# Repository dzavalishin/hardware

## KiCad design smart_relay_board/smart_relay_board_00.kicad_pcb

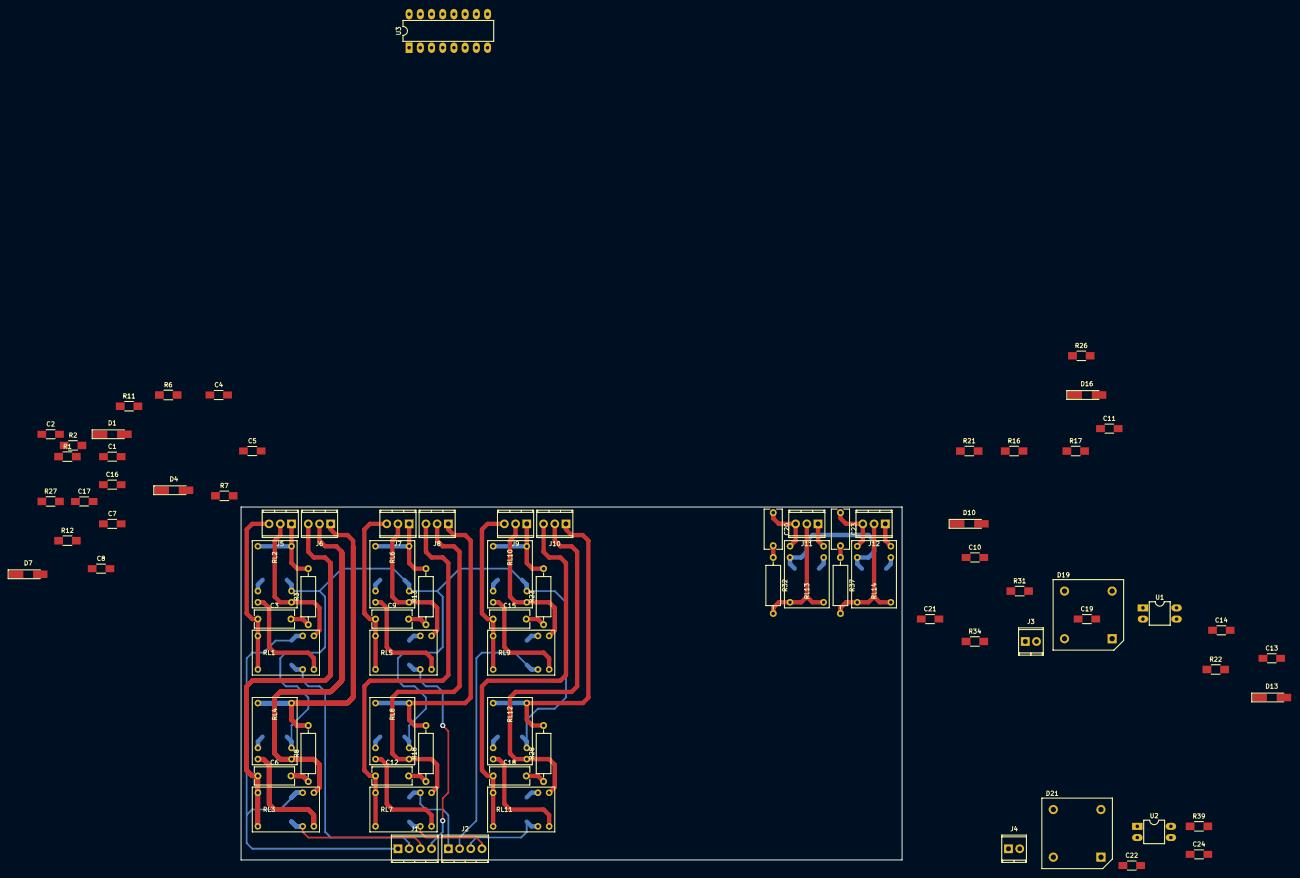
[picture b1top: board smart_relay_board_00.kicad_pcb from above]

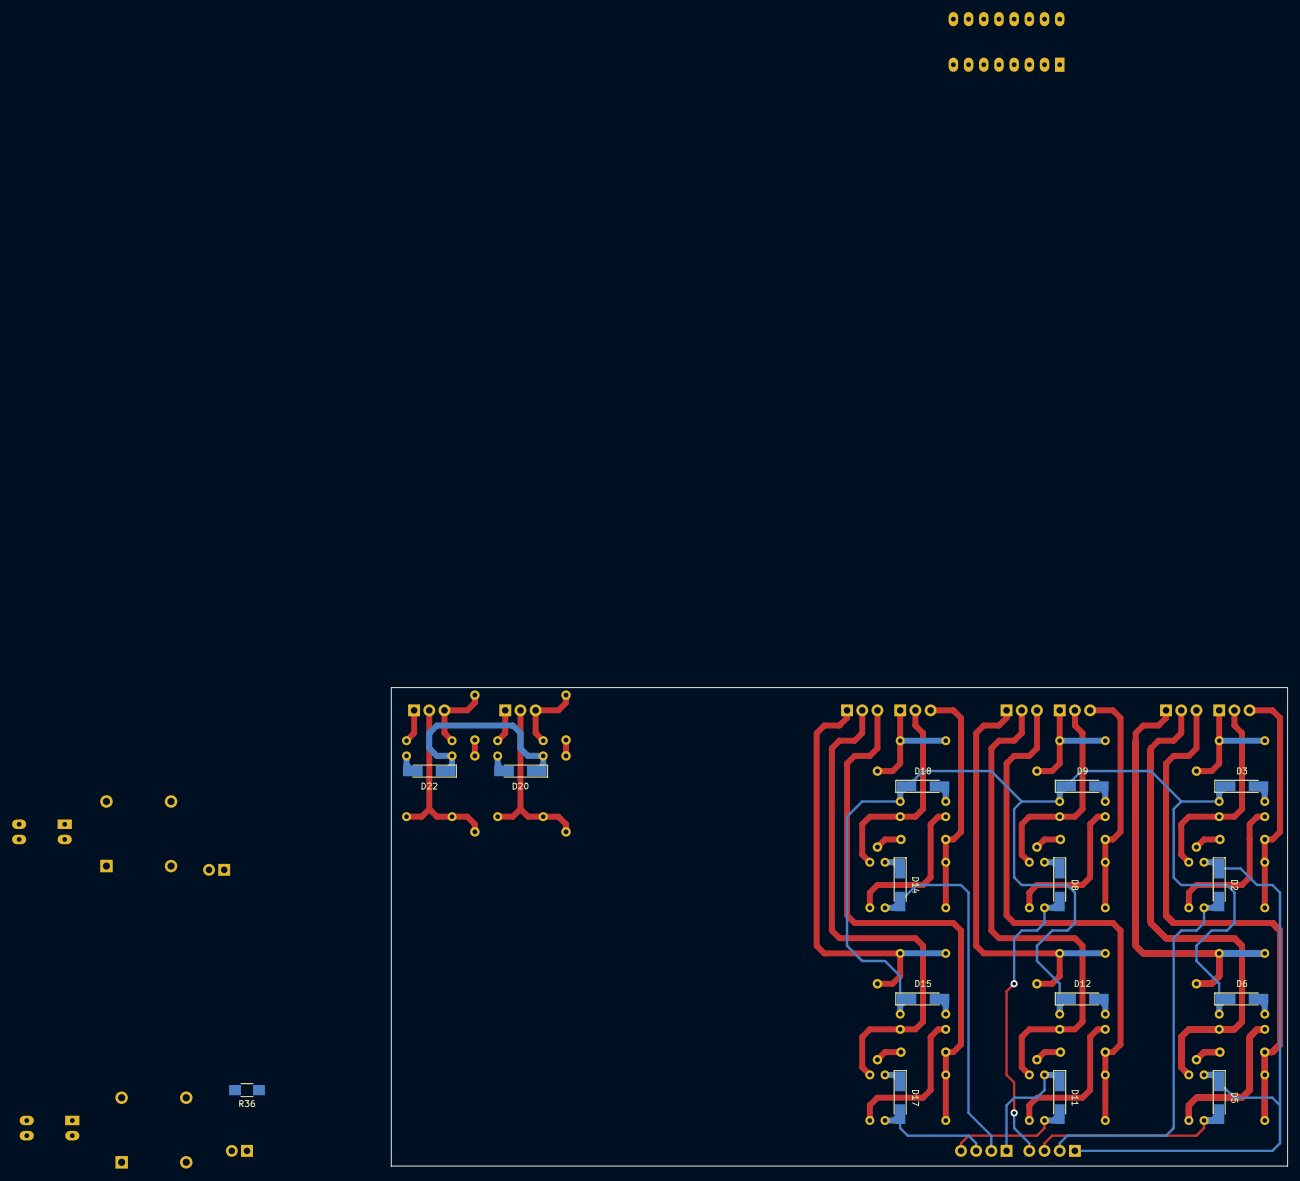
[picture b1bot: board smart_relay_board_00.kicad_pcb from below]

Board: 2 copper layers, 149.9 x 80.0 mm, 99 parts (15 on the bottom side), 81 nets.

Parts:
C1, C2, C4, C5, C7, C8, C10, C11, C13, C14, C16, C17, C19, C21, C22, C24: 0,1; C_1206_HandSoldering
C3, C6, C9, C12, C15, C18, C20, C23: 0,022 x 400v; C_Rect_L9.0mm_W4.0mm_P7.50mm_MKT
D1, D4, D7, D10, D13, D16: 4v7; D_MiniMELF_Handsoldering
D2, D3, D5, D6, D8, D9, D11, D12, D14, D15, D17, D18: 1n4148; D_MiniMELF_Handsoldering
D19, D21: D_Bridge_-A+A; Diode_Bridge_15.7x15.7
D20, D22: 1N4148; D_MiniMELF_Handsoldering
J1: Di0-2; TerminalBlock_Pheonix_MPT-2.54mm_4pol
J2: Di3-5; TerminalBlock_Pheonix_MPT-2.54mm_4pol
J3: Di_6; TerminalBlock_Pheonix_MPT-2.54mm_2pol
J4: Di_7; TerminalBlock_Pheonix_MPT-2.54mm_2pol
J5, J6, J7, J8, J9, J10: Do_Adv; TerminalBlock_Pheonix_MPT-2.54mm_3pol
J11, J12: Do; TerminalBlock_Pheonix_MPT-2.54mm_3pol
R1, R6, R11, R16, R21, R26, R31, R36: 22k; R_1206_HandSoldering
R2, R7, R12, R17, R22, R27, R34, R39: 1k; R_1206_HandSoldering
R3, R8, R13, R18, R23, R28, R32, R37: 100 1w; R_Axial_DIN0309_L9.0mm_D3.2mm_P12.70mm_Horizontal
RL1, RL2, RL3, RL4, RL5, RL6, RL7, RL8, RL9, RL10, RL11, RL12, RL13, RL14: HK4100F; Relay_SPDT_HK4100F
U1, U2: LTV-817; DIP-4_W7.62mm_LongPads
U3: 74HC595; DIP-16_W7.62mm_LongPads

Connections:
+5V: D3.1, D6.1, D9.1, D12.1, D15.1, D18.1, D20.1, D22.1, RL2.5, RL4.5, RL6.5, RL8.5, RL10.5, RL12.5, RL13.5, RL14.5
/Sheet_relay_pair_0/Relay_In_Minus: D2.2, J1.2, R1.1, RL1.2
/Sheet_relay_pair_0/Relay_In_Plus: D2.1, D5.1, D8.1, J1.1, RL1.5, RL3.5, RL5.5
/Sheet_relay_pair_1/Relay_In_Minus: D5.2, J1.3, R6.1, RL3.2
/Sheet_relay_pair_2/Relay_In_Minus: D8.2, J1.4, R11.1, RL5.2
/Sheet_relay_pair_3/Relay_In_Minus: D14.2, J2.2, R21.1, RL9.2
/Sheet_relay_pair_3/Relay_In_Plus: D11.1, D14.1, D17.1, J2.1, RL7.5, RL9.5, RL11.5
/Sheet_relay_pair_4/Relay_In_Minus: D17.2, J2.3, R26.1, RL11.2
/Sheet_relay_pair_5/Relay_In_Minus: D11.2, J2.4, R16.1, RL7.2
/Simple_Di_Do_6/DI_B: D19.2, J3.2
/Simple_Di_Do_6/Di_A: J3.1, R31.2
/Simple_Di_Do_7/DI_B: D21.2, J4.2
/Simple_Di_Do_7/Di_A: J4.1, R36.2
CPU_Di0: C2.1, R2.2
CPU_Di1: C5.1, R7.2
CPU_Di2: C8.1, R12.2
CPU_Di3: C14.1, R22.2
CPU_Di4: C17.1, R27.2
CPU_Di5: C11.1, R17.2
CPU_Di6: C21.1, R34.2
CPU_Di7: C24.1, R39.2
CPU_Do0: D3.2, RL2.2, U3.15
CPU_Do1: D6.2, RL4.2, U3.1
CPU_Do2: D9.2, RL6.2, U3.2
CPU_Do3: D15.2, D18.2, RL10.2, RL12.2, U3.3, U3.4
CPU_Do5: D12.2, RL8.2, U3.5
CPU_Do6: D20.2, RL13.2, U3.6
CPU_Do7: D22.2, RL14.2, U3.7
GND: C1.2, C2.2, C4.2, C5.2, C7.2, C8.2, C10.2, C11.2, C13.2, C14.2, C16.2, C17.2, C21.2, C24.2, D1.2, D4.2, D7.2, D10.2, D13.2, D16.2, U1.3, U2.3, U3.8
unnamed: C1.1, D1.1, R1.2, R2.1
unnamed: C3.1, J5.3, RL1.1, RL1.6
unnamed: C3.2, R3.1
unnamed: C4.1, D4.1, R6.2, R7.1
unnamed: C6.1, J6.3, RL3.1, RL3.6
unnamed: C6.2, R8.1
unnamed: C7.1, D7.1, R11.2, R12.1
unnamed: C9.1, J7.3, RL5.1, RL5.6
unnamed: C9.2, R13.1
unnamed: C10.1, D10.1, R16.2, R17.1
unnamed: C12.1, J8.3, RL7.1, RL7.6
unnamed: C12.2, R18.1
unnamed: C13.1, D13.1, R21.2, R22.1
unnamed: C15.1, J9.3, RL9.1, RL9.6
unnamed: C15.2, R23.1
unnamed: C16.1, D16.1, R26.2, R27.1
unnamed: C18.1, J10.3, RL11.1, RL11.6
unnamed: C18.2, R28.1
unnamed: C19.1, D19.3, U1.1
unnamed: C19.2, D19.1, U1.2
unnamed: C20.1, J11.3, RL13.4
unnamed: C20.2, R32.1
unnamed: C22.1, D21.3, U2.1
unnamed: C22.2, D21.1, U2.2
unnamed: C23.1, J12.3, RL14.4
unnamed: C23.2, R37.1
unnamed: D19.4, R31.1
unnamed: D21.4, R36.1
unnamed: J5.1, R3.2, RL2.1, RL2.6
unnamed: J5.2, RL1.4, RL2.4
unnamed: J6.1, R8.2, RL4.1, RL4.6
unnamed: J6.2, RL3.4, RL4.4
unnamed: J7.1, R13.2, RL6.1, RL6.6
unnamed: J7.2, RL5.4, RL6.4
unnamed: J8.1, R18.2, RL8.1, RL8.6
unnamed: J8.2, RL7.4, RL8.4
unnamed: J9.1, R23.2, RL10.1, RL10.6
unnamed: J9.2, RL9.4, RL10.4
unnamed: J10.1, R28.2, RL12.1, RL12.6
unnamed: J10.2, RL11.4, RL12.4
unnamed: J11.1, RL13.3
unnamed: J11.2, R32.2, RL13.1, RL13.6
unnamed: J12.1, RL14.3
unnamed: J12.2, R37.2, RL14.1, RL14.6
unnamed: R34.1, U1.4
unnamed: R39.1, U2.4
unnamed: RL1.3, RL2.3
unnamed: RL3.3, RL4.3
unnamed: RL5.3, RL6.3
unnamed: RL7.3, RL8.3
unnamed: RL9.3, RL10.3
unnamed: RL11.3, RL12.3

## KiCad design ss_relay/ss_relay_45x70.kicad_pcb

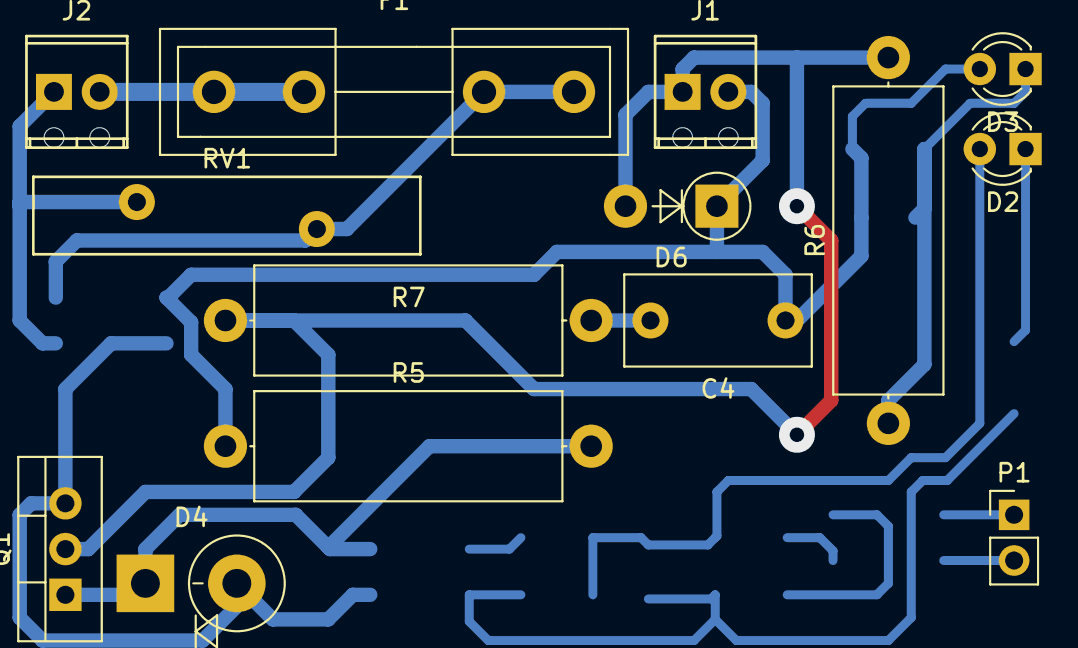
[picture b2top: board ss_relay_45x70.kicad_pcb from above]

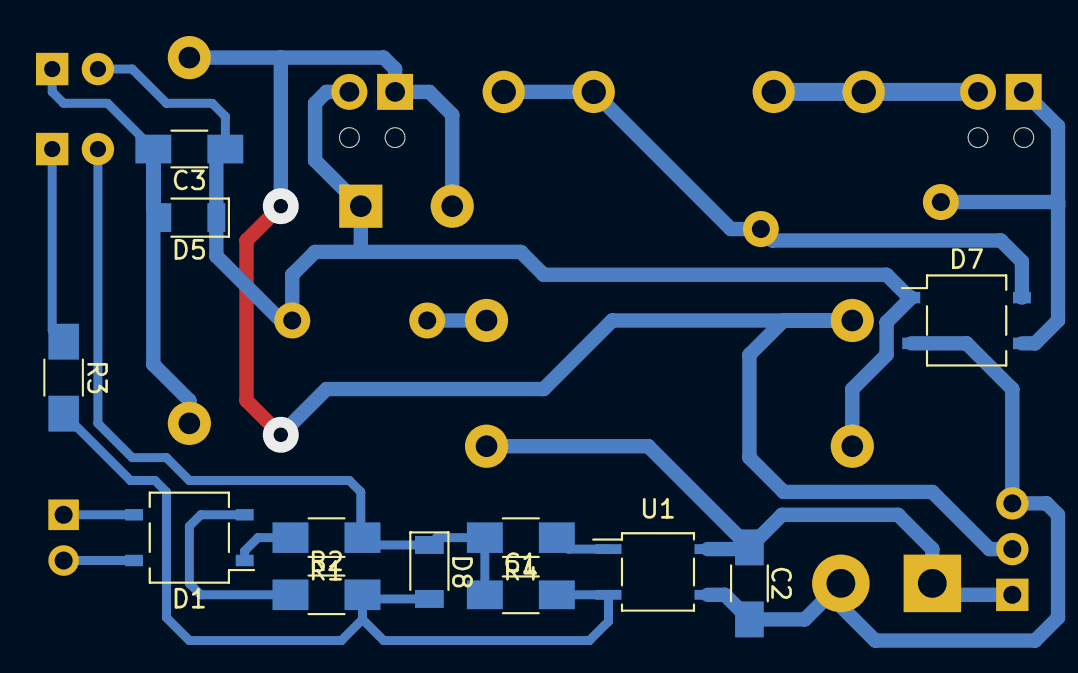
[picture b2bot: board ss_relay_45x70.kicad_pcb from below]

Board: 2 copper layers, 26 parts (12 on the bottom side), 17 nets.

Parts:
C1, C2, C3: 0,1; C_1206_HandSoldering
C4: 0,1 400v; C_Rect_L10.3mm_W5.0mm_P7.50mm_MKS4
D1, D7: MB6S; Diode_Bridge_TO-269AA
D2, D3: LED; LED_D3.0mm
D4: 7,5v 1500a; D_DO-201AD_P5.08mm_Vertical_KathodeUp
D5, D8: 5v6; D_1206
D6: RL206; D_DO-15_P5.08mm_Vertical_AnodeUp
F1: 0,5A; Fuseholder5x20_horiz_open_inline_Type-I
J1: DC Load; TerminalBlock_Pheonix_MPT-2.54mm_2pol
J2: AC220; TerminalBlock_Pheonix_MPT-2.54mm_2pol
P1: CONN_01X02; Pin_Header_Straight_1x02_Pitch2.54mm
Q1: IRF730; TO-220-3_Vertical
R1, R2: 560; R_1206_HandSoldering
R3, R4: 1k; R_1206_HandSoldering
R5, R6: 470k 1W; R_Axial_DIN0617_L17.0mm_D6.0mm_P20.32mm_Horizontal
R7: 56; R_Axial_DIN0617_L17.0mm_D6.0mm_P20.32mm_Horizontal
RV1: 14K391; RV_Disc_D21.5_W4.3_P10
U1: PC817; SOP-4_3.8x4.1mm_Pitch2.54mm

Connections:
unnamed: C1.1, D2.2, D8.1, R1.1, R4.2
unnamed: C1.2, D8.2, R2.2, R3.2, U1.2
unnamed: C2.1, D4.1, Q1.1, R5.2, U1.4
unnamed: C2.2, D4.2, D7.2, Q1.3, U1.3
unnamed: C3.1, C4.1, D3.2, D5.1, D6.1, D7.1, J1.2, R5.1
unnamed: C3.2, D3.1, D5.2, R6.1
unnamed: C4.2, R7.1
unnamed: D1.1, R1.2
unnamed: D1.2, R2.1
unnamed: D1.3, P1.1
unnamed: D1.4, P1.2
unnamed: D2.1, R3.1
unnamed: D6.2, J1.1, Q1.2, R6.2, R7.2
unnamed: D7.3, J2.1, RV1.2
unnamed: D7.4, F1.2, RV1.1
unnamed: F1.1, J2.2
unnamed: R4.1, U1.1

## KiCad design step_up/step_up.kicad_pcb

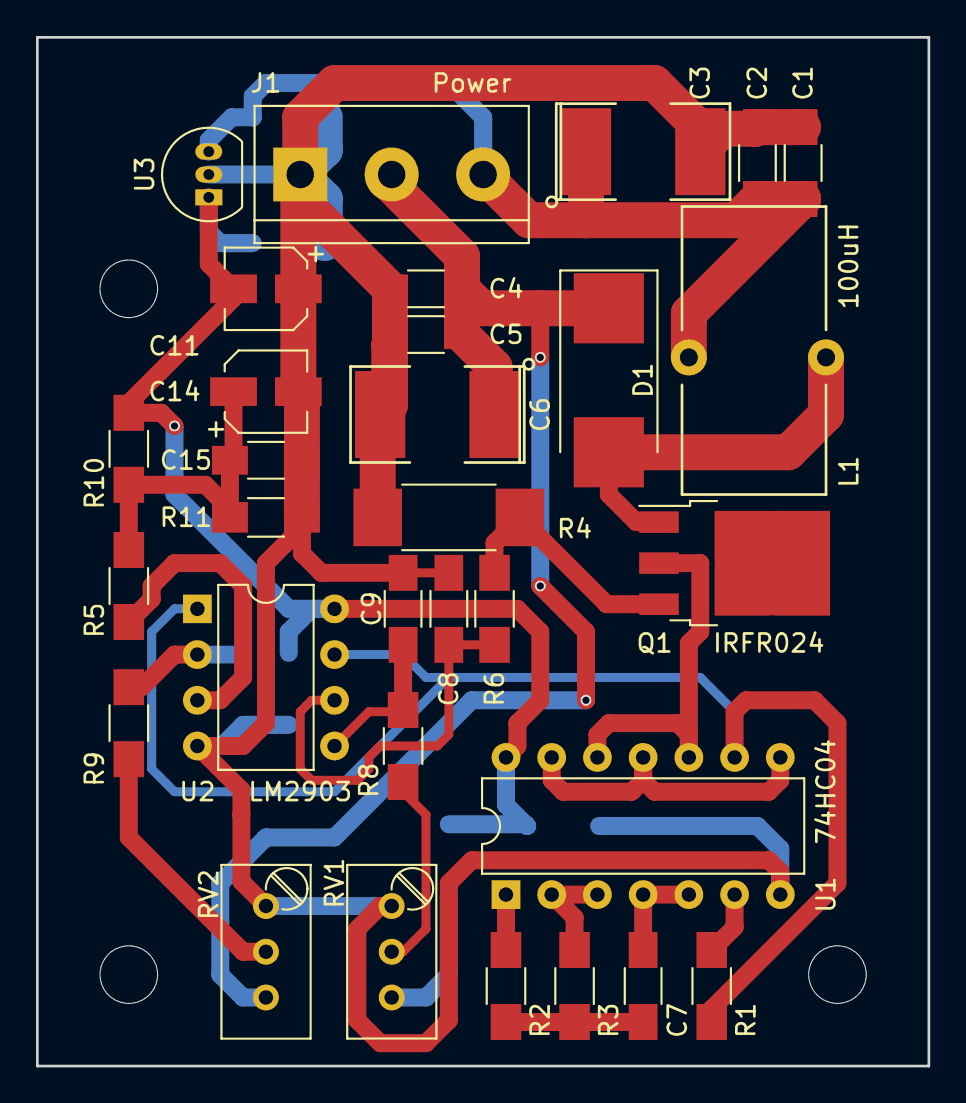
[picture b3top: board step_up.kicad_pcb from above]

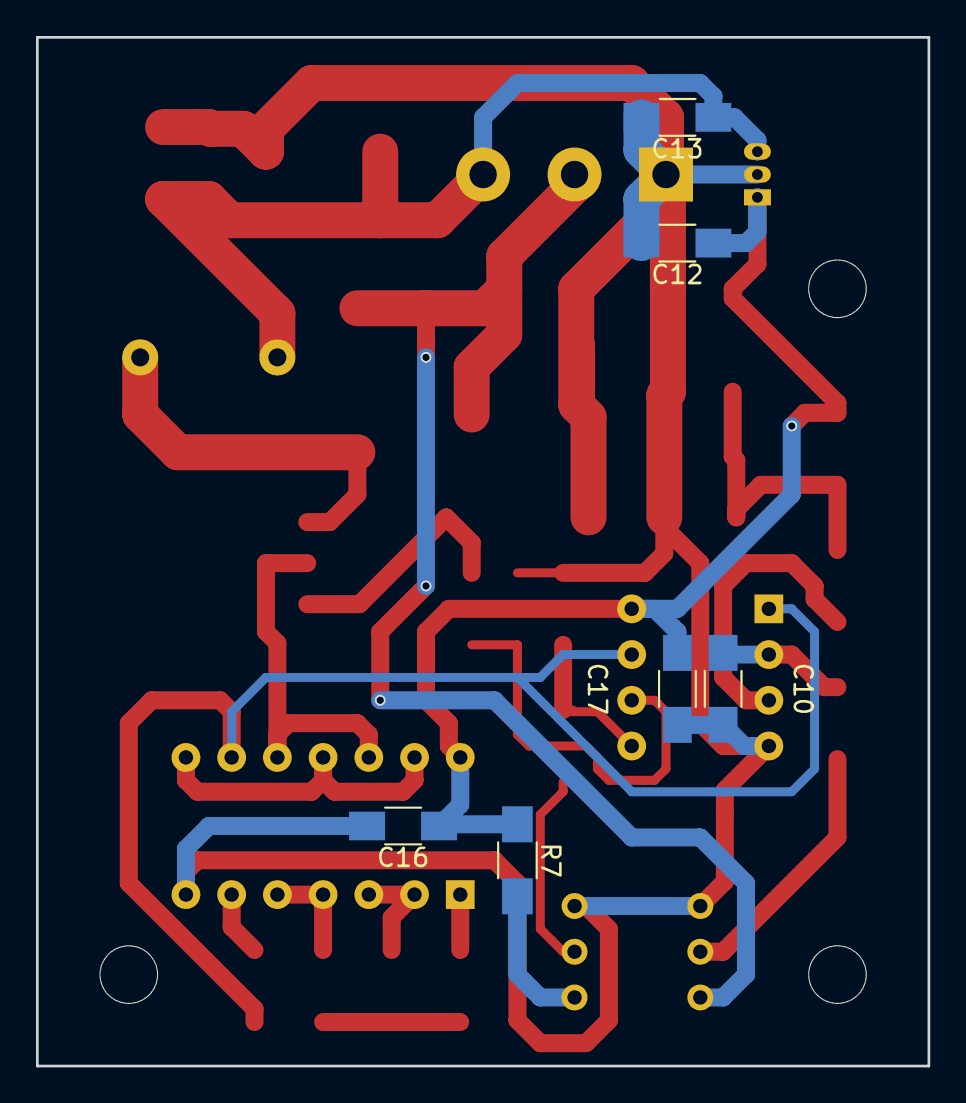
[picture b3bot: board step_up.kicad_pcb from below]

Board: 2 copper layers, 49.5 x 57.1 mm, 37 parts (6 on the bottom side), 22 nets.

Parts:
C1, C4, C8, C9, C14, C16, C17: 0,1; C_1206_HandSoldering
C2, C5: 1,0; C_1206_HandSoldering
C3, C6: 47,0; SMD-2112_Pol
C7: 1n; C_1206_HandSoldering
C10: 4700; C_1206_HandSoldering
C11, C15: 10,0; CP_Elec_4x5.3
C12, C13: 0,33; C_1206_HandSoldering
D1: SB360; D_3220
J1: Power; TerminalBlock_bornier-3_P5.08mm
L1: 100uH; Choke_Toroid_8x16mm_Vertical
Q1: IRFR024; TO-252-3_TabPin2
R1, R6, R8: 1k; R_1206_HandSoldering
R2, R3, R5, R9, R11: 3,3k; R_1206_HandSoldering
R4: 0,1; R_2512_HandSoldering
R7: 200k; R_1206_HandSoldering
R10: 1,5k; R_1206_HandSoldering
RV1, RV2: 50k; Potentiometer_Trimmer_Bourns_3296W
U1: 74HC04; DIP-14_W7.62mm
U2: LM2903; DIP-8_W7.62mm
U3: L78L33; TO-92_Inline_Narrow_Oval

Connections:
+2V5: C14.1, C15.1, R5.2, R10.2, R11.1
+3V3: C11.2, C12.1, C16.1, C17.1, R7.1, R10.1, U1.14, U2.8, U3.1
+6V: C1.1, C2.1, C3.1, C13.1, J1.3, L1.2, U3.3
/+12vOut: C4.1, C5.1, C6.1, D1.1, J1.2, RV2.3
GND: C1.2, C2.2, C3.2, C4.2, C5.2, C6.2, C8.1, C9.2, C10.2, C11.1, C12.2, C13.2, C14.2, C15.2, C16.2, C17.2, J1.1, R4.1, R11.2, RV1.1, RV2.1, U1.7, U2.4, U3.2
unnamed: C7.1, U1.4, U1.5
unnamed: C7.2, R2.2, R3.2
unnamed: C8.2, R6.2, U2.6
unnamed: C9.1, R8.2, U2.5
unnamed: C10.1, R9.2, U2.2
unnamed: D1.2, L1.1, Q1.1
unnamed: Q1.2, U1.10, U1.12
unnamed: Q1.3, R4.2, R6.1
unnamed: R1.1, U1.9, U2.1, U2.7
unnamed: R1.2, U1.6
unnamed: R2.1, U1.1
unnamed: R3.1, U1.2, U1.3
unnamed: R5.1, U2.3
unnamed: R7.2, RV1.3
unnamed: R8.1, RV1.2
unnamed: R9.1, RV2.2
unnamed: U1.8, U1.11, U1.13
